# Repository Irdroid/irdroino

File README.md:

### What is it?

Irdroino is a high quality infrared remote control shield for Arduino. Irdroino is powered by Irdroid’s experience in developing infrared products and it is a open source hardware project.
Use Irdroino to replicate signals from your existing remote controls, assign actions for the tx and rx keys of the shield. Control Air Conditioners, TVs , STBs, Music, and more. The Irdroino will help you also if you develop custom remote controls.

The module is designed with low power consumption considerations in mind and it is suitable for low energy infrared remote controls design and development where you have to provide prolonged periods of unit inactivity (sleep modes) with just several micro amps of power consumption.

The Irdroino comes in a compact form factor, it extends the pin headers of your Arduino and at the same time provides infrared transmitter and receiver capabilities. The Irdroino uses optical signal amplification technique which gives additional boost and extended infrared transmit range. The open source hardware design gives you the freedom to modify Irdroino design and make your own custom IR shield. All the above features make Irdroino better in comparison with the rest of the infrared remote control shields for Arduino available on the market.

# Video

### The Irdroino is compatible with :

* Arduino Boards
* Olimexino Boards

### Features:

* 2 High power IR Leds / uses optical signal amplification /
* 2 buttons for assigning custom IR commands
* High Quality IR receiver IC
* Status LEDs (for transmit and receive)
* Long pin headers that will allow you to use the free pins of your Arduino even if irdroino is on top of your Arduino
* Free and Open Source Software
* Open Source Hardware’s

### Why we made it?

I made this project because I believe in open source software and open source hardware, and I am passionate in developing free and open source infrared modules and things

### What makes it special?

The Irdroino is special, because it uses a unique optical signal amplification which give significantly improoved IR range. This gives a big advantage in comparison with similar products. It is open source hardware which gives the user a freedom and it has a high quality IR receiver IC. There are two sample Arduino Sketches in this repository. The first one is for recording and reproducing IR signals, using the two buttons for transmit and receive (record) remote control buttons. The second exaple sketch turns your Arduino into a PRONTO Hex USB IR Blaster (send / Transmit IR codes via Serial/USB). 

### Get a module:

* [Get a module from Irdroid](https://irdroid.eu/product/irdroino-infrared-shield-arduino/) 
* [Get a module from Tindie](https://www.tindie.com/products/irdroid/irdroino-infrared-shield-for-arduino/)

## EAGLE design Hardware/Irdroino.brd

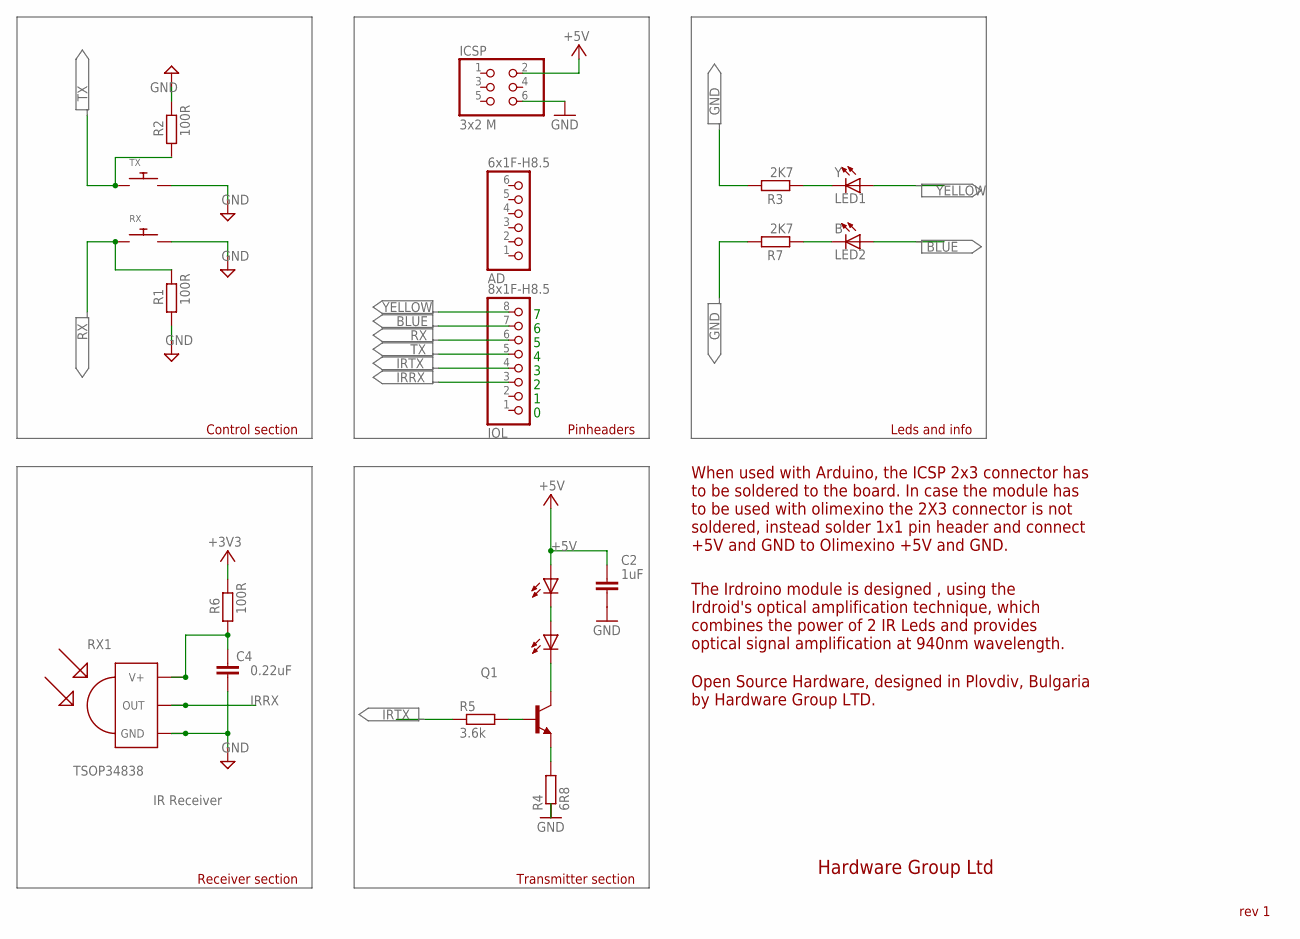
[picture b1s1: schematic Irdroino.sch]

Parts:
AD: 6x1F-H8.5; 1X06
B: LED2; CHIP-LED0805
C2: 1uF; C603@1
C4: 0.22uF; C603
ICSP: 3x2 M; 2X03
IOL: 8x1F-H8.5; 1X08
Q1: TRANSISTOR_BJT_NPN-SOT-23-BCE; SOT-23
R1, R2, R6: 100R; R603
R3, R7: 2K7; R603
R4: 6R8; R1206
R5: 3.6k; R0603
RX: SWITCH_PUSHBUTTONC&K_KSS; BTN_CK_KSS
RX1: TSOP34838; TSOP18XX
TX: SWITCH_PUSHBUTTONC&K_KSS; BTN_CK_KSS
U$5, U$7: IRLED5MM; IRLED_HOLDER
Y: LED1; CHIP-LED0805

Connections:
+5V: C2.1, ICSP.2, R6.2, U$7.A
A: Q1.2 (C), U$5.K (C)
BLUE: B.A, IOL.7
GND: C2.2, C4.2, ICSP.6, R1.1, R2.2, R3.1, R4.1, R7.1, RX.P$2, RX1.GND, TX.P$2
IRRX: IOL.3, RX1.OUT
IRTX: IOL.4, R5.1
K: Q1.3 (E), R4.2
unnamed: U$5.A, U$7.K (C)
unnamed: R3.2, Y.C
unnamed: B.C, R7.2
unnamed: Q1.1 (B), R5.2
unnamed: C4.1, R6.1, RX1.VCC (V+)
RX: IOL.6, R1.2, RX.P$1
TX: IOL.5, R2.1, TX.P$1
YELLOW: IOL.8, Y.A

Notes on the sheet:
RX1
TSOP34838
IR Receiver
Receiver section
Transmitter section
Control section
Leds and info
Pinheaders
Hardware Group Ltd
rev 1
When used with Arduino, the ICSP 2x3 connector has to be soldered to the board. In case the module has to be used with olimexino the 2X3 connector is not soldered, instead solder 1x1 pin header and connect +5V and GND to Olimexino +5V and GND.
The Irdroino module is designed , using the Irdroid's optical amplification technique, which combines the power of 2 IR Leds and provides optical signal amplification at 940nm wavelength.
Open Source Hardware, designed in Plovdiv, Bulgaria by Hardware Group LTD.

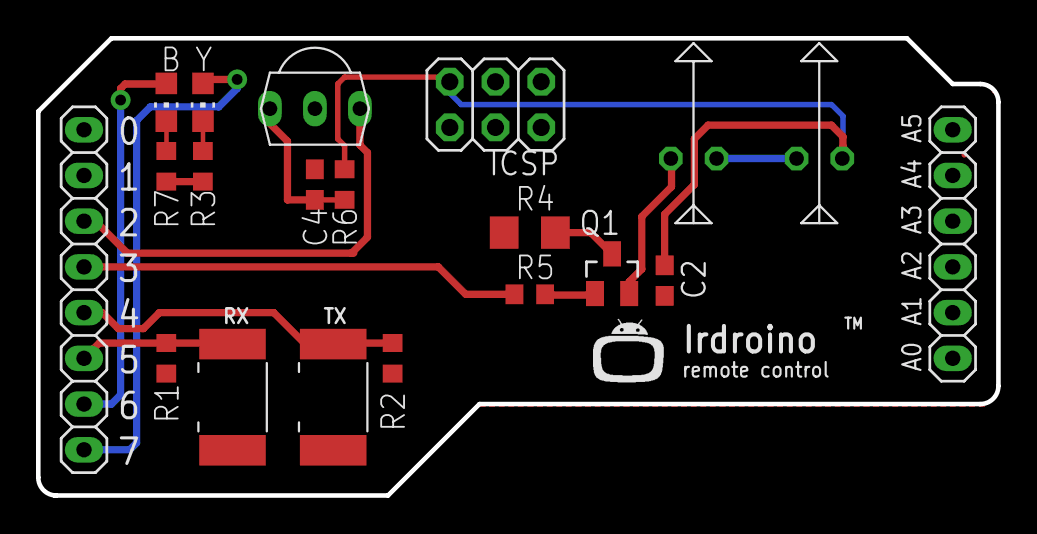
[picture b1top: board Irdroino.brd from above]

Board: 2 copper layers, 53.3 x 25.4 mm, 21 parts (0 on the bottom side), 15 nets.

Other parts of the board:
U$2: IRDROIDLOGO

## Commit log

2017-12-24 Added initial project files
    Added initial project files
2017-12-25 Updated code and Documentation
    Updated code and Documentation
2017-12-26 Updated readme.md with new links
    Updated readme.md with new links
2017-12-26 Updated readme.md
    Updated readme.md
2017-12-26 Added a schematic in PDF
    Added a schematic in PDF in the hardware folder
2017-12-26 Added picture in readme.md
    Added picture in readme.md
2017-12-26 Edited readme.md headings
    Edited readme.md headings
2017-12-26 Another edit
    Another edit
2017-12-26 Changed readme.md
    Changed readme.md
2017-12-26 Another edit
2018-05-02 Added a demo video
    Added Irdroino demo video in readme
2018-05-02 Changed Readme
    Updated Readme
2018-05-22 Added Irdroino Pronto USB IR Blaster sketch
    Added Irdroino Pronto USB IR Blaster sketch
2018-05-25 Updated Readme.md to include Irdroino function PRONTO USB IR Blaster
    Updated Readme.md to include Irdroino function PRONTO USB IR Blaster
2022-12-10 Added Blast_ir command-line tools
2022-12-10 Added Software Readme.md
